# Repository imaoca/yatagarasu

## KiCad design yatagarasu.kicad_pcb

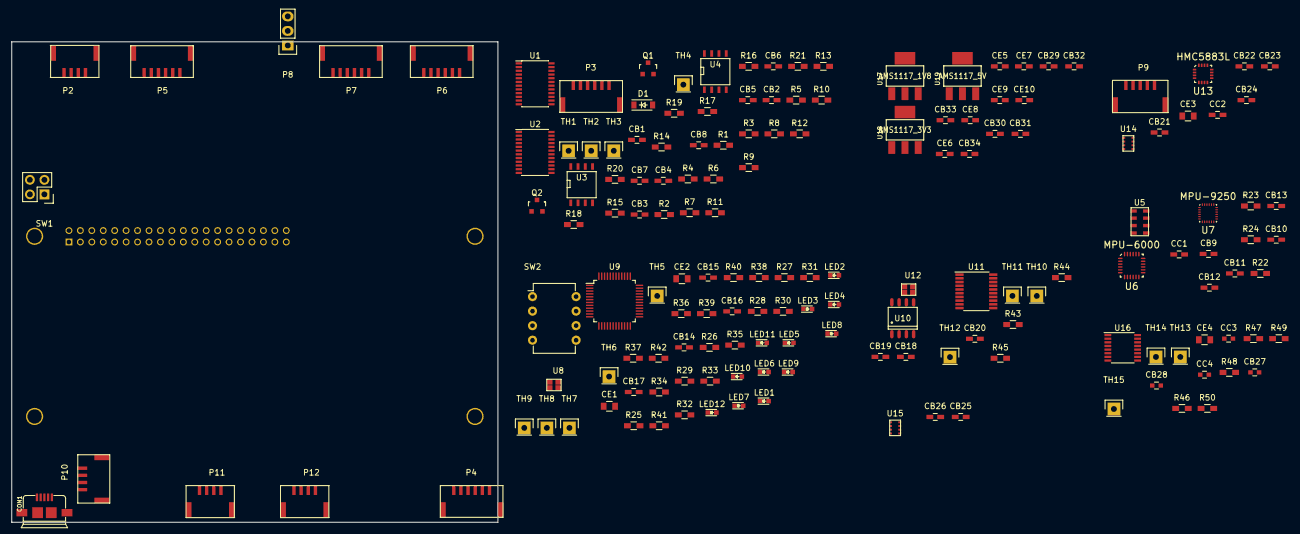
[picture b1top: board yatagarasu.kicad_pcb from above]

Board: 2 copper layers, 85.0 x 84.0 mm, 162 parts (1 on the bottom side), 124 nets, no tracks yet.

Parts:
CB1, CB2, CB3, CB4, CB5, CB6, CB7, CB8, CB9, CB10, CB11, CB12, CB13, CB14, CB15, CB16, CB17, CB18, CB19, CB20, CB21, CB22, CB23, CB24, CB25, CB26, CB29, CB30, CB31, CB32, CB33, CB34: 104; C_0603_HandSoldering
CB27, CB28: 104; C_0603
CC1: 2200pF; C_0603_HandSoldering
CC2: 0.22uF; C_0603_HandSoldering
CC3, CC4: 39pF; C_0603
CE1: 1uF; C_0805
CE2: 3.3uF; C_0805
CE3: 4.7uF; C_0805
CE4: 10uF; C_0805
CE5, CE6, CE7, CE8, CE9, CE10: 22uF; C_0603_HandSoldering
CON1: CONSOLE; USB_MICRO_B_ST-USB-001E
D1: 1N4148; SOD-123
LED1, LED2, LED3, LED4, LED5, LED6, LED7, LED8, LED9, LED10, LED11, LED12: LED; LED_0603
P1: CONN_02X20; Pin_Header_Straight_2x20_Pitch2mm
P2: +12V_IN; GH_4P_side
P3: ttyAMA2; GH_6P_side
P4: ttyMAX3; GH_6P_side
P5: ttyMAX2; GH_6P_side
P6: ttyMAX1; GH_6P_side
P7: ttyMAX0; GH_6P_side
P8: CAN; Pin_Header_Straight_1x03
P9: PCA9685_OUT; GH_5P_side
P10: I2C1_0; GH_4P_side
P11: I2C1_1; GH_4P_side
P12: I2C1_2; GH_4P_side
Q1, Q2: MMBT3904; SOT-23
R1, R2, R4, R17, R18, R20, R21: 2K2; R_0603_HandSoldering
R3, R5, R6, R7, R8, R9, R10, R11, R22, R23, R24, R33, R43, R45: 47K; R_0603_HandSoldering
R12, R13, R14, R15, R35, R36, R37, R38: 22K; R_0603_HandSoldering
R16, R19: 200K; R_0603_HandSoldering
R25, R26, R27, R28, R29, R30, R31, R32, R39, R40, R41, R42: 470; R_0603_HandSoldering
R34, R47: 10K; R_0603_HandSoldering
R44: 120; R_0603_HandSoldering
R46, R48: 22; R_0603_HandSoldering
R49, R50: 220; R_0603_HandSoldering
SW1: RESET; Pin_Header_Straight_2x02
SW2: DIP_SW4; DIP-8_W7.62mm
TH1, TH2, TH3, TH4, TH5, TH6, TH7, TH8, TH9, TH10, TH11, TH12, TH13, TH14, TH15: TH; Pin_Header_Straight_1x01
U1, U2: 8T245; TSSOP-24_4.4x7.8mm_Pitch0.65mm
U3, U4: PCA9306; SOIC-8-N
U5: MS5611-01BA03
U6: MPU-6000
U7: MPU-9250
U8, U12: SG-210STF_16MHz; SG-210STF
U9: MAX14830; TQFP-48_7x7mm_Pitch0.5mm
U10: MCB2551-I/SN; SO-8
U11: MCB2515; TSSOP-20_4.4x6.5mm_Pitch0.65mm
U13: HMC5883L
U14: BME280; BMP280
U15: 2SMPB-02A; BMP280
U16: FT230XS; SSOP-16_3.9x4.9mm_Pitch0.635mm
U17: AMS1117_1V8; SOT223
U18: AMS1117_3V3; SOT223
U19: AMS1117_5V; SOT223

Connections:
+1V8: CB1.1, CB4.1, CB5.1, CB7.1, CB30.1, CE6.1, R1.1, R6.1, R7.1, R8.1, R9.1, R10.1, R11.1, U1.1, U1.2, U2.23, U2.24, U3.2, U4.2, U16.3, U17.2
+3V3: CB2.1, CB3.1, CB9.1, CB10.1, CB11.1, CB12.1, CB13.1, CB14.1, CB15.1, CB16.1, CB17.1, CB19.1, CB20.1, CB21.1, CB22.1, CB23.1, CB24.1, CB25.1, CB26.1, CB32.1, CE2.1, CE8.1, LED1.2, LED2.2, LED3.2, LED4.2, LED5.2, LED6.2, LED7.2, LED8.2, P3.1, P4.1, P5.1, P6.1, P7.1, P9.1, P10.1, P11.1, P12.1, R2.1, R4.1, R16.1, R17.1, R18.1, R19.1, R20.1, R21.1, R22.1, R23.1, R24.1, R33.1, R34.1, R35.1, R36.1, R37.1, R38.1, R43.1, R45.1, U1.23, U1.24, U2.1, U2.2, U5.1, U6.8, U6.13, U7.8, U7.13, U8.1, U8.4, U9.1, U9.2, U9.9, U9.43, U9.47, U11.18, U12.4, U13.2, U13.4, U13.13, U14.2, U14.6, U14.8, U15.2, U15.6, U15.8, U18.2
+5V: CB18.1, CB34.1, CE10.1, U10.3, U19.2
/AMS1117s/SYSDC_IN: CE5.1, CE7.1, CE9.1, P1.36, P1.38, P2.1, P2.2, U17.3, U18.3, U19.3
/Console/+5F: CB27.1, CE4.1, CON1.1, U16.12
/Console/USBDM: CC4.1, CON1.2, R46.2
/Console/USBDP: CC3.1, CON1.3, R48.2
/can/MISO: U2.3, U5.6, U6.9, U7.9, U9.3, U11.15
/can/MOSI: U1.20, U5.7, U6.24, U7.24, U9.6, U11.14
/can/SCLK: U1.21, U5.8, U6.23, U7.23, U9.4, U11.13
/can/~CAN_CS: R43.2, U1.15, U11.16
/can/~CAN_IRQ: R45.2, U2.5, U11.12
/can/~RESET: Q2.3, R4.2, U9.8, U11.17
/i2c0/I2C0_SCL_3V3: P9.2, R17.2, U3.6, U13.1, U14.4
/i2c0/I2C0_SDA_3V3: P9.3, R18.2, U3.5, U13.16, U14.3
/i2c0/PCA9685_OE: P9.4, U1.14
/i2c1/I2C1_SCL_3V3: P10.2, P11.2, P12.2, R20.2, U4.6, U15.4
/i2c1/I2C1_SDA_3V3: P10.3, P11.3, P12.3, R21.2, U4.5, U15.3
/max/gpio0: R25.2, U9.11
/max/gpio1: R26.2, U9.12
/max/gpio2: R27.2, U9.13
/max/gpio3: R28.2, U9.14
/max/gpio4: R29.2, U9.19
/max/gpio5: R30.2, U9.20
/max/gpio6: R31.2, U9.21
/max/gpio7: R32.2, U9.22
/max/gpio8: R35.2, SW2.1, U9.27
/max/gpio9: R36.2, SW2.2, U9.28
/max/gpio10: R37.2, SW2.3, U9.29
/max/gpio11: R38.2, SW2.4, U9.30
/max/gpio12: R39.2, TH6.1, U9.35
/max/gpio13: R40.2, TH7.1, U9.36
/max/gpio14: R41.2, TH8.1, U9.37
/max/gpio15: R42.2, TH9.1, U9.38
/max/~MAX14830_CS: R33.2, U1.16, U9.5
/max/~MAX14830_IRQ: R34.2, U2.4, U9.7
/spi/~MPU600_CS: R23.2, U1.17, U6.22
/spi/~MPU9250_CS: R24.2, U1.18, U7.22
/spi/~MS5611_CS: R22.2, U1.19, U5.4, U5.5
GND: CB1.2, CB2.2, CB3.2, CB4.2, CB5.2, CB6.2, CB7.2, CB8.2, CB9.2, CB10.2, CB11.2, CB12.2, CB13.2, CB14.2, CB15.2, CB16.2, CB17.2, CB18.2, CB19.2, CB20.2, CB21.2, CB22.2, CB23.2, CB24.2, CB25.2, CB26.2, CB27.2, CB28.2, CB29.2, CB30.2, CB31.2, CB32.2, CB33.2, CB34.2, CC1.2, CC3.2, CC4.2, CE1.2, CE2.2, CE3.2, CE4.2, CE5.2, CE6.2, CE7.2, CE8.2, CE9.2, CE10.2, CON1.5, CON1.6, CON1.7, CON1.8, CON1.9, LED9.1, LED10.1, LED11.1, LED12.1, P1.1, P1.2, P1.39, P2.3, P2.4, P3.6, P4.6, P5.6, P6.6, P7.6, P9.5, P10.4, P11.4, P12.4, Q1.2, Q2.2, R12.2, R13.2, R14.2, R15.2, R47.1, SW1.2, SW2.5, SW2.6, SW2.7, SW2.8, U1.11, U1.12, U1.13, U2.11, U2.12, U2.13, U3.1, U4.1, U5.2, U5.3, U6.18, U7.18, U8.2, U9.10, U9.46, U10.2, U10.8, U11.9, U12.2, U13.9, U13.11, U14.1, U14.5, U14.7, U15.1, U15.5, U15.7, U16.5, U16.13, U17.1, U18.1, U19.1
GPIO_A: P1.23, R7.2, U1.6
GPIO_B: P1.24, R8.2, U1.7
GPIO_C: P1.25, R9.2, U1.8
GPIO_D: P1.26, R10.2, U1.9
GPIO_E: P1.27, R11.2, U1.10
GPIO_F: P1.28, U2.20
I2C0_SCL: P1.15, U3.3
I2C0_SDA: P1.17, U3.4
I2C1_SCL: P1.19, U4.3
I2C1_SDA: P1.21, U4.4
unnamed: CB6.1, R16.2, U3.7, U3.8
unnamed: CB8.1, R19.2, U4.7, U4.8
unnamed: CB28.1, U16.10, U16.11
unnamed: CC1.1, U6.21
unnamed: CC2.1, U13.12
unnamed: CC2.2, U13.8
unnamed: CE1.1, U9.48
unnamed: CE3.1, U13.10
unnamed: D1.1, Q1.3, R2.2, R5.1, U2.22
unnamed: D1.2, R1.2, U1.22
unnamed: LED1.1, R25.1
unnamed: LED2.1, R26.1
unnamed: LED3.1, R27.1
unnamed: LED4.1, R28.1
unnamed: LED5.1, R29.1
unnamed: LED6.1, R30.1
unnamed: LED7.1, R31.1
unnamed: LED8.1, R32.1
unnamed: LED9.2, R39.1
unnamed: LED10.2, R40.1
unnamed: LED11.2, R41.1
unnamed: LED12.2, R42.1
unnamed: P1.7, U2.18
unnamed: P1.35, R3.1
unnamed: P3.3, U2.6
unnamed: P4.2, U9.42
unnamed: P4.3, U9.41
unnamed: P4.4, U9.40
unnamed: P4.5, U9.39
unnamed: P5.2, U9.34
unnamed: P5.3, U9.33
unnamed: P5.4, U9.32
unnamed: P5.5, U9.31
unnamed: P6.2, U9.26
unnamed: P6.3, U9.25
unnamed: P6.4, U9.24
unnamed: P6.5, U9.23
unnamed: P7.2, U9.18
unnamed: P7.3, U9.17
unnamed: P7.4, U9.16
unnamed: P7.5, U9.15
unnamed: P8.1, R44.2, U10.7
unnamed: P8.3, R44.1, U10.6
unnamed: Q1.1, R3.2
unnamed: Q2.1, R5.2
unnamed: R12.1, U2.7
unnamed: R13.1, U2.8
unnamed: R14.1, U2.9
unnamed: R15.1, U2.10
unnamed: R46.1, U16.9
unnamed: R47.2, U16.6
unnamed: R48.1, U16.8
unnamed: R49.2, U16.7
unnamed: R50.2, U16.16
unnamed: TH1.1, U2.17
unnamed: TH2.1, U2.16
unnamed: TH3.1, U2.15
unnamed: TH4.1, U2.14
unnamed: TH5.1, U8.3, U9.45
unnamed: TH10.1, U11.3
unnamed: TH11.1, U10.5
unnamed: TH12.1, U11.8, U12.3
unnamed: TH13.1, U16.2
unnamed: TH14.1, U16.15
unnamed: TH15.1, U16.14
unnamed: U10.1, U11.1
unnamed: U10.4, U11.2
PCM_DO: P1.20, U2.19
PWR_BTN: P1.4, R49.1
RST_BTN: P1.6, R50.1, SW1.1
SPI0_CS: P1.12, R6.2, U1.5
SPI0_MISO: P1.10, U2.21
SPI0_MOSI: P1.14, U1.4
SPI0_SCK: P1.8, U1.3

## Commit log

2016-05-01 :boom::camel: Added .gitattributes & .gitignore files
2016-05-01 create yatagarasu project now
    copy inital files from yatagarasu20160407a.
